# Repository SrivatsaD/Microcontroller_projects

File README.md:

STM32 microcontroller project:

Hello! Welcome to my Microcontroller project portfolio. Here I will list all the projects that I have done in microcontroller design and embedded systems. 
Feel free to check it out and contact me if you would like to provide advice or an opportunity to contribute to your own projects.

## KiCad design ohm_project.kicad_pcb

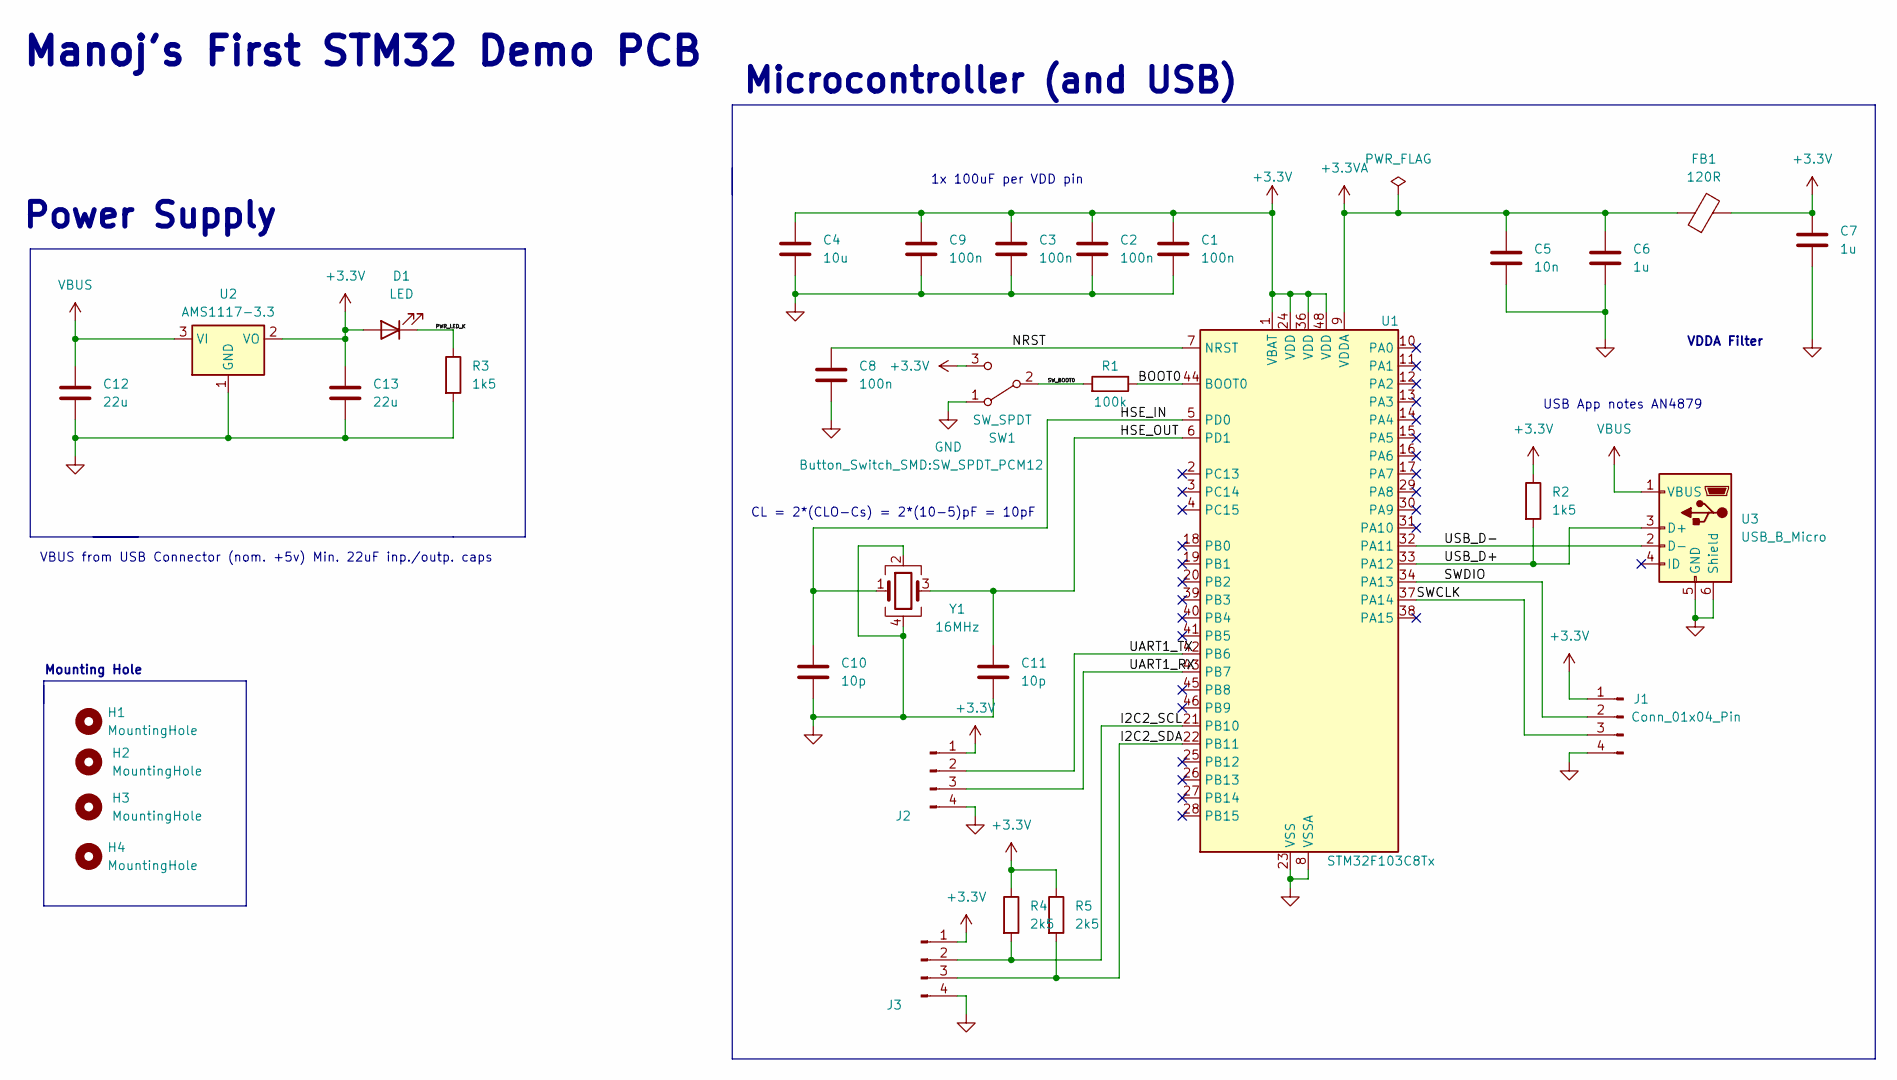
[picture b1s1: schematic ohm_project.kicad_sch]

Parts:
C1, C2, C3, C8, C9: 100n; C_0402_1005Metric
C4: 10u; C_0201_0603Metric
C5: 10n; C_0402_1005Metric
C6, C7: 1u; C_0603_1608Metric
C10, C11: 10p; C_0402_1005Metric
C12, C13: 22u; C_0805_2012Metric
D1: LED; LED_0603_1608Metric
FB1: 120R; L_0603_1608Metric
H1, H2, H3, H4: MountingHole; MountingHole_2.2mm_M2
J1, J2, J3: Conn_01x04_Pin; PinHeader_1x04_P2.54mm_Vertical
R1: 100k; R_0402_1005Metric
R2, R3: 1k5; R_0402_1005Metric
R4, R5: 2k5; R_0402_1005Metric
SW1: SW_SPDT; SW_SPDT_PCM12
U1: STM32F103C8Tx; LQFP-48_7x7mm_P0.5mm
U2: AMS1117-3.3; SOT-223-3_TabPin2
U3: USB_B_Micro; USB_Micro-B_Wuerth_629105150521
Y1: 16MHz; Crystal_SMD_3225-4Pin_3.2x2.5mm

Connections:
+3.3V: C1.1, C2.1, C3.1, C4.1, C7.1, C9.1, C13.1, D1.2 (A), FB1.2, J1.1, J2.1, J3.1, R2.1, R4.1, R5.1, SW1.3 (C), U1.1 (VBAT), U1.24 (VDD), U1.36 (VDD), U1.48 (VDD), U2.2 (VO)
+3.3VA: C5.1, C6.1, FB1.1, U1.9 (VDDA)
/BOOT0: R1.1, U1.44 (BOOT0)
/HSE_IN: C10.1, U1.5 (PD0), Y1.1
/HSE_OUT: C11.1, U1.6 (PD1), Y1.3
/I2C2_SCL: J3.2, R4.2, U1.21 (PB10)
/I2C2_SDA: J3.3, R5.2, U1.22 (PB11)
/NRST: C8.1, U1.7 (NRST)
/PWR_LED_K: D1.1 (K), R3.1
/SWCLK: J1.3, U1.37 (PA14)
/SWDIO: J1.2, U1.34 (PA13)
/SW_BOOT0: R1.2, SW1.2 (B)
/UART1_RX: J2.3, U1.43 (PB7)
/UART1_TX: J2.2, U1.42 (PB6)
/USB_D+: R2.2, U1.33 (PA12), U3.3 (D+)
/USB_D-: U1.32 (PA11), U3.2 (D-)
GND: C1.2, C2.2, C3.2, C4.2, C5.2, C6.2, C7.2, C8.2, C9.2, C10.2, C11.2, C12.2, C13.2, J1.4, J2.4, J3.4, R3.2, SW1.1 (A), U1.8 (VSSA), U1.23 (VSS), U1.35 (VSS), U1.47 (VSS), U2.1 (GND), U3.5 (GND), U3.6 (Shield), Y1.2, Y1.4
VBUS: C12.1, U2.3 (VI), U3.1 (VBUS)

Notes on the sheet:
Microcontroller (and USB)
Mounting Hole
VDDA Filter
CL = 2*(CLO-Cs) = 2*(10-5)pF = 10pF
USB App notes AN4879
1x 100uF per VDD pin
Power Supply
Manoj's First STM32 Demo PCB
VBUS from USB Connector (nom. +5v) Min. 22uF inp./outp. caps

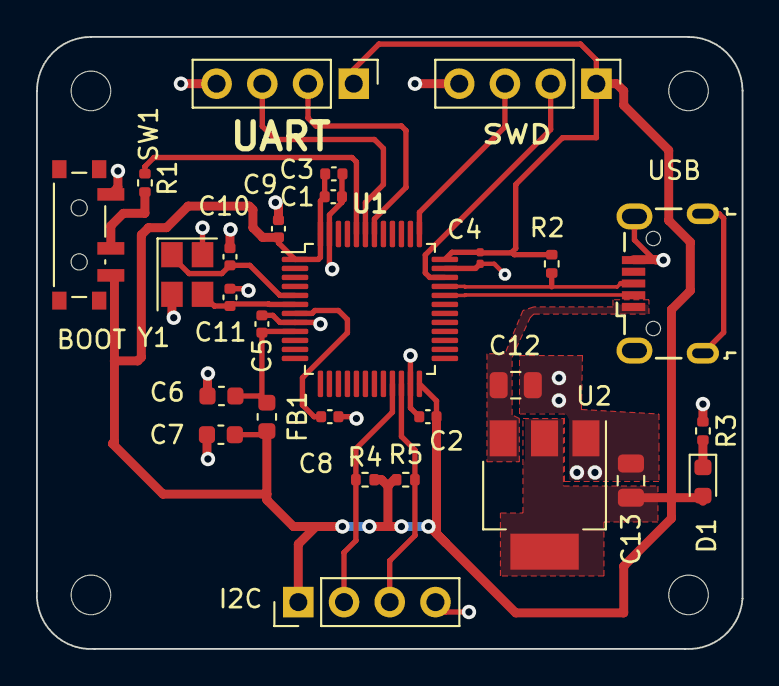
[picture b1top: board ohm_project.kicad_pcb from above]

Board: 2 copper layers, 39.2 x 34.0 mm, 32 parts (0 on the bottom side), 18 nets.
